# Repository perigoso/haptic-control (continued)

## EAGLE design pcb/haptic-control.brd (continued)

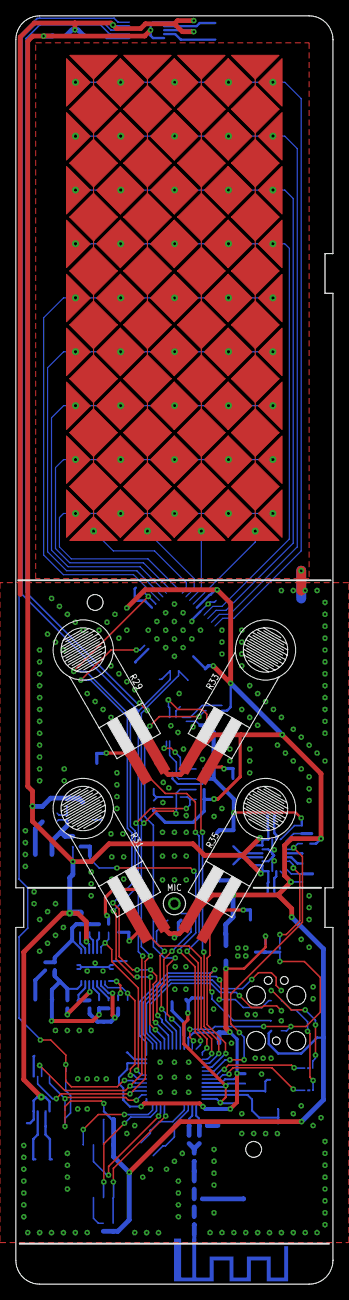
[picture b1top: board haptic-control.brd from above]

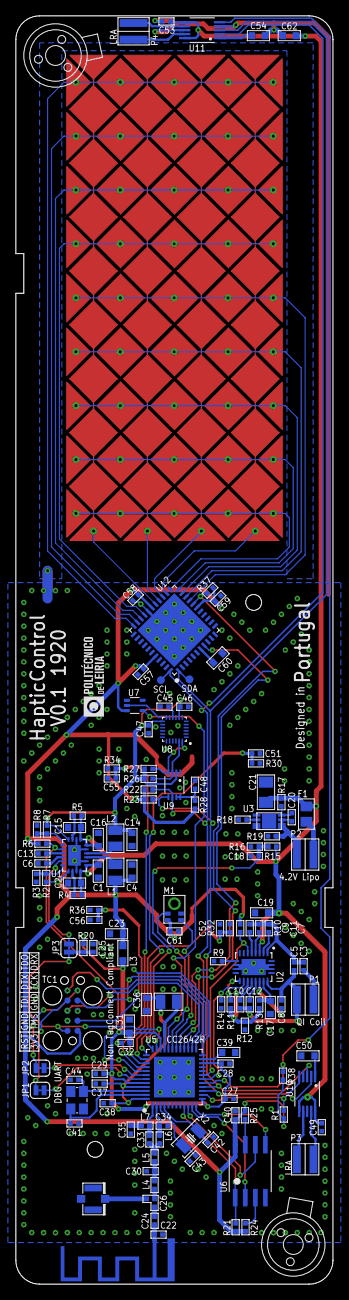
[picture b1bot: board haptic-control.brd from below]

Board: 2 copper layers, 40.0 x 160.0 mm, 152 parts (135 on the bottom side), 104 nets.

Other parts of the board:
U$1, U$2: G0825001
U$3: DESIGNEDINPT

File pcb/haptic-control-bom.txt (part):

Partlist exported from /home/rafael/Development/haptic-control/pcb/haptic-control.sch at 14/05/19 21:21

Qty Value                      Device                     Package                     Parts                                                                                             Description                                     
1   100                        RESISTOR_0402              _0402                       R17                                                                                               Resistors                                       
13  100k                       RESISTOR_0402              _0402                       R1, R4, R5, R6, R10, R13, R15, R20, R21, R24, R25, R37, R38                                       Resistors                                       
20  100n                       MLCC_0402                  _0402                       C3, C20, C25, C27, C28, C29, C32, C37, C38, C40, C45, C46, C47, C48, C49, C53, C57, C58, C59, C61 KEMET’s X7R dielectric features a 125°C maximum 
1   100u                       MLCC_1206                  _1206                       C21                                                                                               KEMET’s X7R dielectric features a 125°C maximum 
1   10M                        RESISTOR_0402              _0402                       R19                                                                                               Resistors                                       
1   10k                        RESISTOR_0402              _0402                       R14                                                                                               Resistors                                       
2   10n                        MLCC_0402                  _0402                       C7, C8                                                                                            KEMET’s X7R dielectric features a 125°C maximum 
2   10u                        MLCC0603                   0603_WAVE                   C60, C62                                                                                          KEMET’s X7R dielectric features a 125°C maximum 
3   12p                        MLCC_0402                  _0402                       C35, C42, C43                                                                                     KEMET’s X7R dielectric features a 125°C maximum 
1   12p                        MLCC_SEL                   _0402_SEL                   C26                                                                                                                                               
1   140                        RESISTOR_0402              _0402                       R12                                                                                               Resistors                                       
1   158k                       RESISTOR_0402              _0402                       R8                                                                                                Resistors                                       
1   1k                         RESISTOR_0402              _0402                       R18                                                                                               Resistors                                       
1   1k2                        RESISTOR_0402              _0402                       R11                                                                                               Resistors                                       
1   1n                         MLCC_0402                  _0402                       C5                                                                                                KEMET’s X7R dielectric features a 125°C maximum 
3   1p                         MLCC_0402                  _0402                       C30, C33, C34                                                                                     KEMET’s X7R dielectric features a 125°C maximum 
1   1p8                        MLCC_0402                  _0402                       C24                                                                                               KEMET’s X7R dielectric features a 125°C maximum 
2   1u                         INDUCTOR_NC_0806           _0806                       L1, L2                                                                                                                                            
5   1u                         MLCC0603                   0603_WAVE                   C1, C16, C39, C50, C54                                                                            KEMET’s X7R dielectric features a 125°C maximum 
1   2.4GHZTRACE-15.2MM         2.4GHZTRACE-15.2MM         TRACE_ANTENNA_2.4GHZ_15.2MM E1                                                                                                Chip antenna                                    
1   200k                       RESISTOR_0402              _0402                       R28                                                                                               Resistors                                       
2   22n                        MLCC_0402                  _0402                       C9, C10                                                                                           KEMET’s X7R dielectric features a 125°C maximum 
3   22u                        MLCC0603                   0603_WAVE                   C23, C31, C36                                                                                     KEMET’s X7R dielectric features a 125°C maximum 
4   2P-PAD_1X3.5               2P-PAD_1X3.5               PAD1X3_5MM-2P               P1, P2, P3, P4                                                                                                                                    
1   2k43                       RESISTOR_0402              _0402                       R9                                                                                                Resistors                                       
2   2n                         INDUCTOR_NC_0402           _0402                       L4, L5                                                                                                                                            
2   2n4                        INDUCTOR_NC_0402           _0402                       L6, L7                                                                                                                                            
4   3.4k                       RESISTOR_0402              _0402                       R30, R32, R34, R36                                                                                Resistors                                       
1   301k                       RESISTOR_0402              _0402                       R7                                                                                                Resistors                                       
1   309k                       RESISTOR_0402              _0402                       R2                                                                                                Resistors                                       
1   32.768kHz                  CRYSTAL2-SMD-3215          2-SMD-3215                  X2                                                                                                                                                
2   470n                       MLCC_0402                  _0402                       C11, C12                                                                                          KEMET’s X7R dielectric features a 125°C maximum 
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
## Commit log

2019-05-07 root commit
2019-05-07 initial pcb constraints, and initial sch
2019-05-07 removed eagle temporary files
2019-05-07 Reorganized
2019-05-07 Added more datasheets
2019-05-08 minor sch value modifications, and ic additions; minor pcb constraints changes
2019-05-08 Hand merged previous commits: Added CC26x2 reference design Added antenna matching Connected labels to touch IC Added keepouts for the antenna Added more references/info to the board and schematic
2019-05-08 removed rogue file
2019-05-08 added battery and coil pads, changed mcu orientation
2019-05-08 Add LRA datasheet
2019-05-08 added LRA drivers, added FSRs
2019-05-08 TODO: qi, mcu connect
2019-05-09 Add QI and conect MCU
2019-05-09 added notes to schematic
2019-05-10 minor component placement and silkscreen changes
2019-05-10 silkscreen experiments
2019-05-12 Add pcap touch panel
2019-05-12 Updated FSR package with provided design dimensions
2019-05-12 Added IPL logo
2019-05-13 touch matrix connections
2019-05-13 touch matrix gnd plane minor change
2019-05-13 i2c level shifter sch fix
2019-05-13 removed hardware MPU pwr switch
2019-05-13 Nothing to do Needs revision
2019-05-13 minor routing changes
2019-05-14 finished routing
2019-05-15 changed component values, created bom, changed bat prot ic
2019-05-15 finished bom, exported gerbers
2019-05-21 created a simplified bom for order
2019-09-19 doc update
